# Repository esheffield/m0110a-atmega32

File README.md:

# m0110a-atmega32

## Background
This repo contains the schematic, pcb, and code for a drop-in replacement module for the controller in the Macintosh Plus m0110a keyboard. This controller is often damage or destroyed thanks to Apple's bizarre decision to use a cable that that *looks* like a telephone handset cable and uses the same connectors but is *wired differently*. If a user tried to use a phone handset cable in place of the original, this would feed reversed polarity power to the controller and kill it.

This replacement is based on the ATMega32 microcontroller. This controller was chosen due to the high number of GPIO pins available. The keyboard uses most of these, with a 10 x 8 matrix, four additional lines for Shift, Caps Lock, Command, and Option keys, and two communication lines for a total of 24 required lines. To aid in debugging if necessary in the future, the dedicated serial TxD and RxD lines are reserved and broken out to an optional header on the module.

The module also provides a standard 6-pin ISP connection. Thanks to the layout of keyboard, it's possible to access the ISP and Serial headers by removing the spacebar.

## Limitations
At this time, this module will only work in the m0110a keyboard as included with the Macintosh Plus. I don't know if the 128 / 512 keyboard and numeric keypad use the same controller. I understand that the keypad in particular has to act as a intermediary between the keyboard and Mac. I expect this work could be adapted, but at the least would require updated code if not changes to the hardware itself.

## License

The design and code are licensed under Apache 2.0.

## Attribution and Thanks

The code for communication with the Macintosh is based on the work of Tomasz Rękawek (https://github.com/trekawek), specifically his project adapting a PS2 keyboard to a Mac Plus (https://github.com/trekawek/mac-plus-ps2). Many thanks to Tomasz for his valuable work!

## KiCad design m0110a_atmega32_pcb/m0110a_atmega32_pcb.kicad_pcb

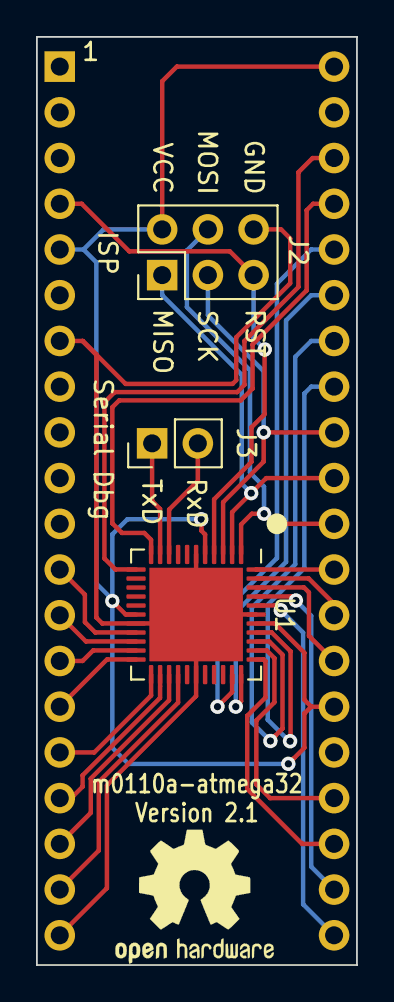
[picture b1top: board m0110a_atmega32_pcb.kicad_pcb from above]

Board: 2 copper layers, 17.8 x 51.6 mm, 4 parts (0 on the bottom side), 29 nets.

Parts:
J1: Conn_01x40_Pin; Header_2.54_W15.24mm
J2: ISP; PinHeader_2x03_P2.54mm_Vertical
J3: Serial; PinHeader_1x02_P2.54mm_Vertical
U1: ATmega32A-M; QFN-44-1EP_7x7mm_P0.5mm_EP5.2x5.2mm

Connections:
+5V: J1.5, J1.26, J1.40, J2.2, U1.5 (VCC), U1.17 (VCC), U1.38 (VCC)
/CMD: J1.36, U1.32 (PA5)
/COL0: J1.19, U1.26 (PC7)
/COL1: J1.18, U1.25 (PC6)
/COL2: J1.17, U1.24 (PC5)
/COL3: J1.16, U1.23 (PC4)
/COL4: J1.15, U1.22 (PC3)
/COL5: J1.14, U1.21 (PC2)
/COL6: J1.13, U1.20 (PC1)
/COL7: J1.12, U1.19 (PC0)
/KB_CLK: J1.37, U1.11 (PD2)
/KB_DATA: J1.38, U1.12 (PD3)
/LOCK: J1.24, U1.35 (PA2)
/OPT: J1.35, U1.33 (PA4)
/ROW0: J1.21, U1.40 (PB0)
/ROW1: J1.22, U1.41 (PB1)
/ROW2: J1.27, U1.42 (PB2)
/ROW3: J1.28, U1.43 (PB3)
/ROW4: J1.29, U1.44 (PB4)
/ROW5: J1.30, J2.4, U1.1 (PB5)
/ROW6: J1.31, J2.1, U1.2 (PB6)
/ROW7: J1.32, J2.3, U1.3 (PB7)
/ROW8: J1.33, U1.37 (PA0)
/ROW9: J1.34, U1.36 (PA1)
/RXD: J3.2, U1.9 (PD0)
/SHIFT: J1.23, U1.34 (PA3)
/TXD: J3.1, U1.10 (PD1)
GNDREF: J1.7, J1.20, J2.6, U1.6 (GND), U1.18 (GND), U1.28 (GND), U1.39 (GND), U1.45 (GND)
RESET: J1.4, J2.5, U1.4 (~RESET)

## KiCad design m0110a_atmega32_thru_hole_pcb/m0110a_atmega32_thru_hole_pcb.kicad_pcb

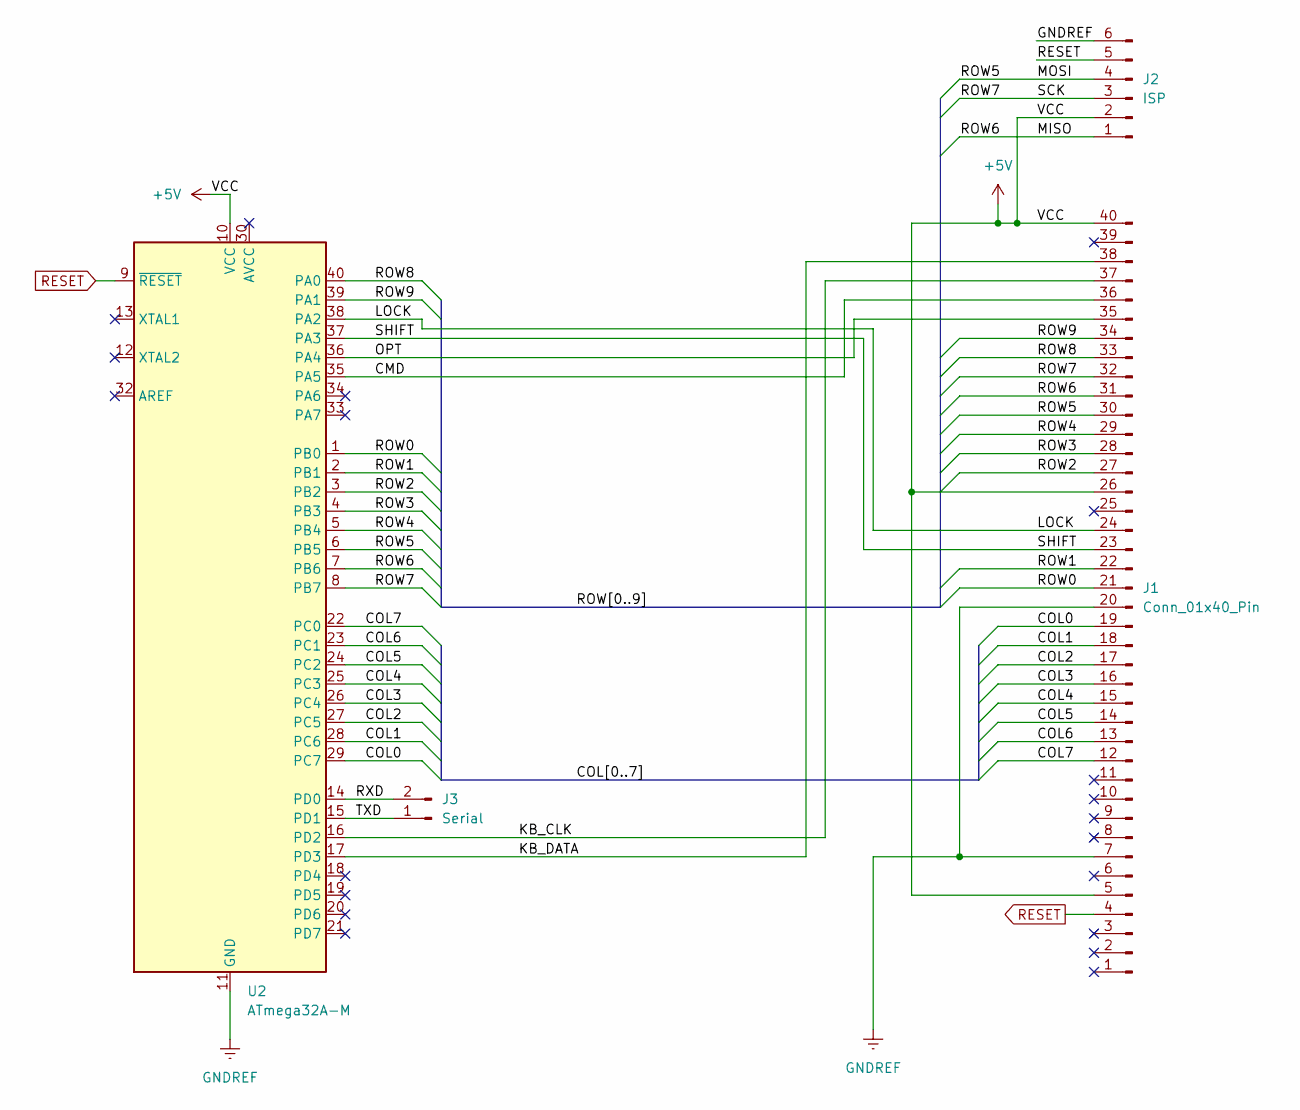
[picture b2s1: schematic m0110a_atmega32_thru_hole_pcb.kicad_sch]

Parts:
J1: Conn_01x40_Pin; Header_2.54_W15.24mm
J2: ISP; PinHeader_2x03_P2.54mm_Vertical
J3: Serial; PinHeader_1x02_P2.54mm_Vertical
U2: ATmega32A-M; DIP-40_W15.24mm

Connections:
+5V: J1.5, J1.26, J1.40, J2.2, U2.10 (VCC)
/CMD: J1.36, U2.35 (PA5)
/COL0: J1.19, U2.29 (PC7)
/COL1: J1.18, U2.28 (PC6)
/COL2: J1.17, U2.27 (PC5)
/COL3: J1.16, U2.26 (PC4)
/COL4: J1.15, U2.25 (PC3)
/COL5: J1.14, U2.24 (PC2)
/COL6: J1.13, U2.23 (PC1)
/COL7: J1.12, U2.22 (PC0)
/KB_CLK: J1.37, U2.16 (PD2)
/KB_DATA: J1.38, U2.17 (PD3)
/LOCK: J1.24, U2.38 (PA2)
/OPT: J1.35, U2.36 (PA4)
/ROW0: J1.21, U2.1 (PB0)
/ROW1: J1.22, U2.2 (PB1)
/ROW2: J1.27, U2.3 (PB2)
/ROW3: J1.28, U2.4 (PB3)
/ROW4: J1.29, U2.5 (PB4)
/ROW5: J1.30, J2.4, U2.6 (PB5)
/ROW6: J1.31, J2.1, U2.7 (PB6)
/ROW7: J1.32, J2.3, U2.8 (PB7)
/ROW8: J1.33, U2.40 (PA0)
/ROW9: J1.34, U2.39 (PA1)
/RXD: J3.2, U2.14 (PD0)
/SHIFT: J1.23, U2.37 (PA3)
/TXD: J3.1, U2.15 (PD1)
GNDREF: J1.7, J1.20, J2.6, U2.11 (GND), U2.31 (GND)
RESET: J1.4, J2.5, U2.9 (~RESET)

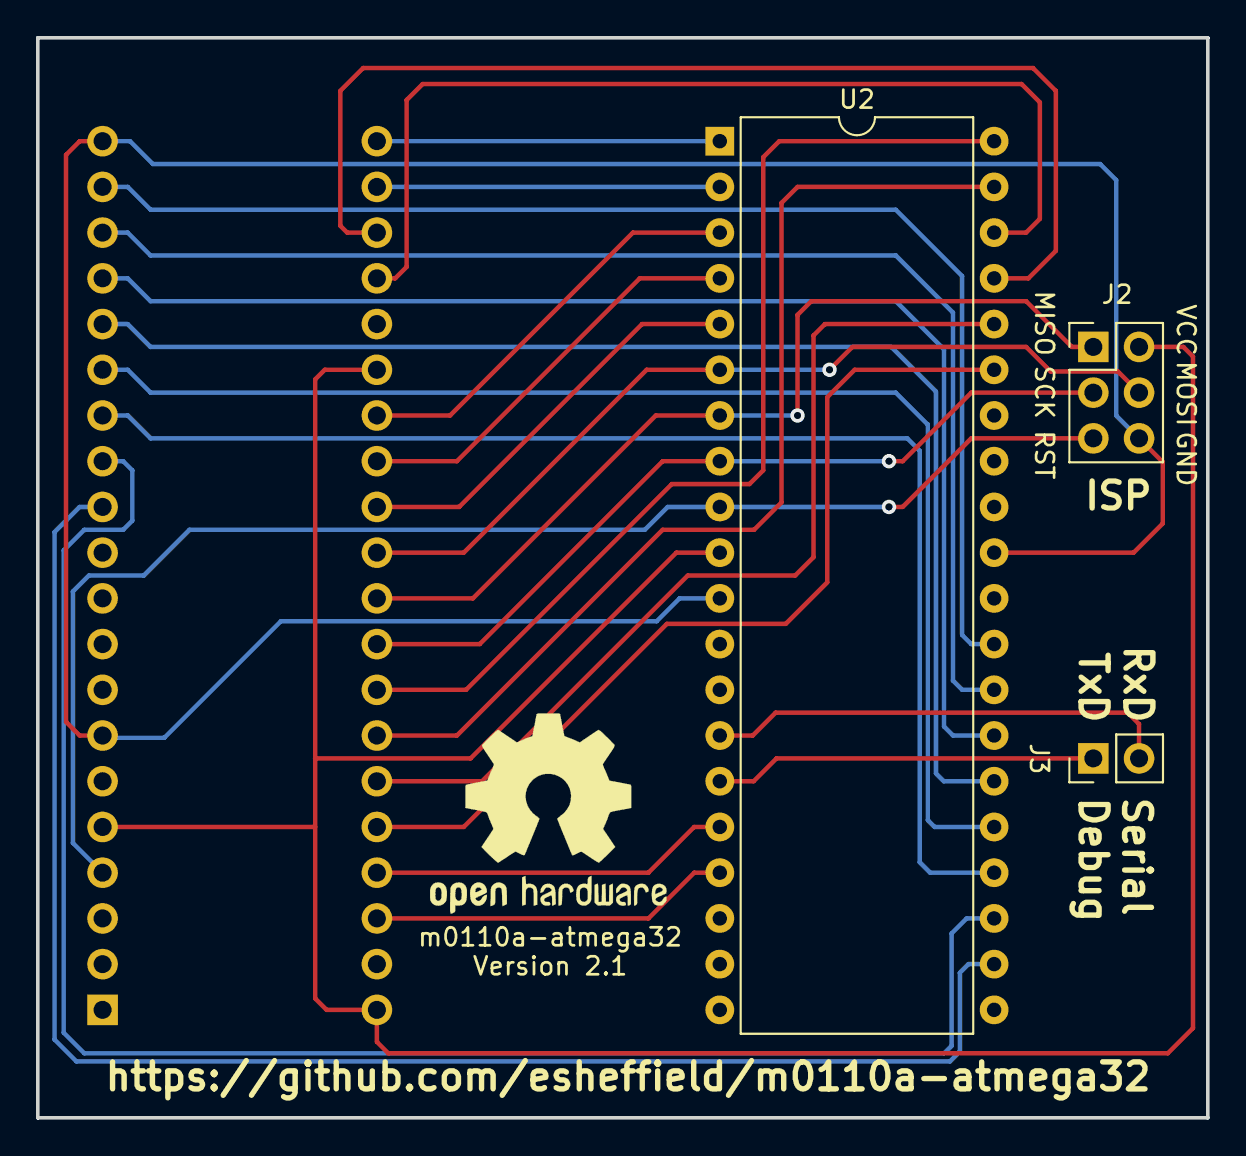
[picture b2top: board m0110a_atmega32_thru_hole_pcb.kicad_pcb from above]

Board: 2 copper layers, 65.0 x 60.0 mm, 4 parts (1 on the bottom side), 29 nets.

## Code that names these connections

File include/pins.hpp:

#include <Arduino.h>

#ifndef PINS_HPP
#define PINS_HPP

#define CLK_PIN PIN_PD2
#define DATA_PIN PIN_PD3

#define CMD_PIN PIN_PA5
#define OPT_PIN PIN_PA4
#define LCK_PIN PIN_PA2
#define SHF_PIN PIN_PA3

byte ROW_PINS[] = {PIN_PB0, PIN_PB1, PIN_PB2, PIN_PB3, PIN_PB4, PIN_PB5, PIN_PB6, PIN_PB7, PIN_PA0, PIN_PA1};
byte COL_PINS[] = {PIN_PC7, PIN_PC6, PIN_PC5, PIN_PC4, PIN_PC3, PIN_PC2, PIN_PC1, PIN_PC0};
byte MOD_PINS[] = {CMD_PIN, OPT_PIN, LCK_PIN, SHF_PIN};

#endif

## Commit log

2024-01-03 Initial code commit
2024-01-19 Add m0110a.h, read modifiers
2024-01-20 Disable JTAG on port C, Read column values
2024-01-20 Iterate over rows
2024-01-20 Fully scan keys other than modifiers
2024-01-21 Begin adding protocol support, start refactoring
2024-01-21 Continue refactoring to keyboard class
2024-01-21 Completed keyboard scanning refactoring, clean up protocol code a bit
2024-01-21 Works! Code can use a bit of cleanup still but fully functions.
2024-01-28 Rearrange some pins for easier PCB layout
2024-01-28 Create LICENSE
    Add Apache 2.0 license file
2024-01-28 Add README file
2024-01-28 Add schematic and PCB design
2024-01-28 Update ignore for KiCAD files
2024-01-30 Updated PCB to use more readily available parts
2024-02-05 Fixed shift locking when certain numpad keys are pressed
    Added thru-hold PCB design
2024-02-05 Switched from external to internal clocking
2024-02-09 Removed unneeded resistor and ground connections
2024-02-09 Swapped data and clk for easier layout. V 2.1
2024-02-15 Added gerbers (PCBWay rules)
2024-02-24 KP equal fix, serial debug cleanups
    - KP equal needs a SHIFT prefix code as well, wasn't listed in the Mac docs
    - Wrapped all debugging prints with ifdefs on SERIAL_DEBUG
    - Added commented out SERIAL_DEBUG definition to platformio.ini for easy
    reference
    Note: I attempted to created wrappers around the Serial.printX
    functions, but they aren't actually variadic and would have meant
2024-02-25 Updated PCBs
    - Increased hole size on 40 pin connector to accomodate standard pin headers
    - Moved ISP connector on SMD board to clear support under spacebar
    - Improved labeling on thru-hole board for ISP connector
